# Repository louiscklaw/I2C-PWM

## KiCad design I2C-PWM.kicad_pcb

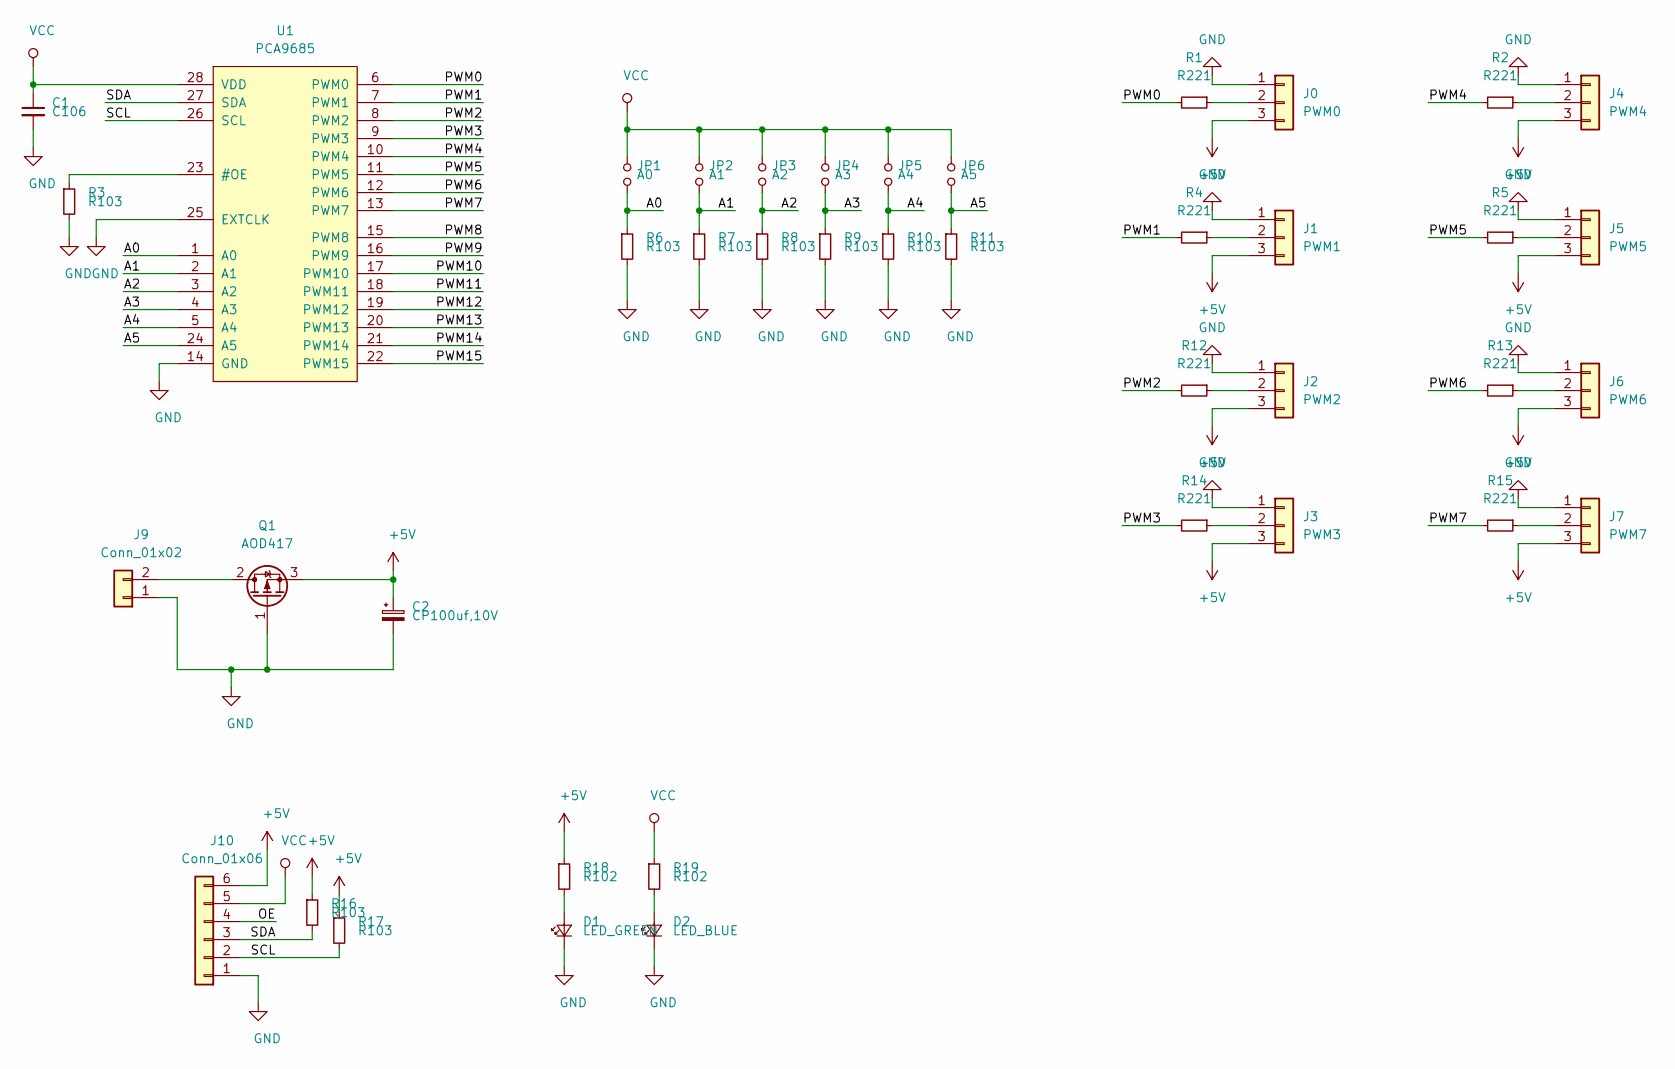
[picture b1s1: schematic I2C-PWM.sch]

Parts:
C1: C106; C_0805_2012Metric_Pad1.15x1.40mm_HandSolder
C2: CP100uf,10V; CP_Elec_6.3x5.2
D1: LED_GREEN; LED_0805_2012Metric_Pad1.15x1.40mm_HandSolder
D2: LED_BLUE; LED_0805_2012Metric_Pad1.15x1.40mm_HandSolder
J0: PWM0; PinHeader_1x03_P2.54mm_Vertical
J1: PWM1; PinHeader_1x03_P2.54mm_Vertical
J2: PWM2; PinHeader_1x03_P2.54mm_Vertical
J3: PWM3; PinHeader_1x03_P2.54mm_Vertical
J4: PWM4; PinHeader_1x03_P2.54mm_Vertical
J5: PWM5; PinHeader_1x03_P2.54mm_Vertical
J6: PWM6; PinHeader_1x03_P2.54mm_Vertical
J7: PWM7; PinHeader_1x03_P2.54mm_Vertical
J9: Conn_01x02; PinHeader_1x02_P2.54mm_Vertical
J10: Conn_01x06; PinHeader_1x06_P2.54mm_Vertical
JP1: A0; SolderJumper-2_P1.3mm_Open_TrianglePad1.0x1.5mm
JP2: A1; SolderJumper-2_P1.3mm_Open_TrianglePad1.0x1.5mm
JP3: A2; SolderJumper-2_P1.3mm_Open_TrianglePad1.0x1.5mm
JP4: A3; SolderJumper-2_P1.3mm_Open_TrianglePad1.0x1.5mm
JP5: A4; SolderJumper-2_P1.3mm_Open_TrianglePad1.0x1.5mm
JP6: A5; SolderJumper-2_P1.3mm_Open_TrianglePad1.0x1.5mm
Q1: AOD417; TO-252-2
R1, R2, R4, R5, R12, R13, R14, R15: R221; R_0805_2012Metric_Pad1.15x1.40mm_HandSolder
R3, R6, R7, R8, R9, R10, R11, R16, R17: R103; R_0805_2012Metric_Pad1.15x1.40mm_HandSolder
R18, R19: R102; R_0805_2012Metric_Pad1.15x1.40mm_HandSolder
U1: PCA9685; TSSOP-28_4.4x9.7mm_P0.65mm

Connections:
+5V: C2.1, J0.3, J1.3, J2.3, J3.3, J4.3, J5.3, J6.3, J7.3, J10.6, Q1.3 (S), R16.1, R17.1, R18.1
/A0: JP1.2, R6.1, U1.1 (A0)
/A1: JP2.2, R7.1, U1.2 (A1)
/A2: JP3.2, R8.1, U1.3 (A2)
/A3: JP4.2, R9.1, U1.4 (A3)
/A4: JP5.2, R10.1, U1.5 (A4)
/A5: JP6.2, R11.1, U1.24 (A5)
/OE: J10.4
/PWM0: R1.2, U1.6 (PWM0)
/PWM1: R4.2, U1.7 (PWM1)
/PWM2: R12.2, U1.8 (PWM2)
/PWM3: R14.2, U1.9 (PWM3)
/PWM4: R2.2, U1.10 (PWM4)
/PWM5: R5.2, U1.11 (PWM5)
/PWM6: R13.2, U1.12 (PWM6)
/PWM7: R15.2, U1.13 (PWM7)
/PWM8: U1.15 (PWM8)
/PWM9: U1.16 (PWM9)
/PWM10: U1.17 (PWM10)
/PWM11: U1.18 (PWM11)
/PWM12: U1.19 (PWM12)
/PWM13: U1.20 (PWM13)
/PWM14: U1.21 (PWM14)
/PWM15: U1.22 (PWM15)
/SCL: J10.2, R17.2, U1.26 (SCL)
/SDA: J10.3, R16.2, U1.27 (SDA)
GND: C1.2, C2.2, D1.1 (K), D2.1 (K), J0.1, J1.1, J2.1, J3.1, J4.1, J5.1, J6.1, J7.1, J9.1, J10.1, Q1.1 (G), R3.2, R6.2, R7.2, R8.2, R9.2, R10.2, R11.2, U1.14 (GND), U1.25 (EXTCLK)
unnamed: D1.2 (A), R18.2
unnamed: D2.2 (A), R19.2
unnamed: J0.2, R1.1
unnamed: J1.2, R4.1
unnamed: J2.2, R12.1
unnamed: J3.2, R14.1
unnamed: J4.2, R2.1
unnamed: J5.2, R5.1
unnamed: J6.2, R13.1
unnamed: J7.2, R15.1
unnamed: J9.2, Q1.2 (D)
unnamed: R3.1, U1.23 (#OE)
VCC: C1.1, J10.5, JP1.1, JP2.1, JP3.1, JP4.1, JP5.1, JP6.1, R19.1, U1.28 (VDD)

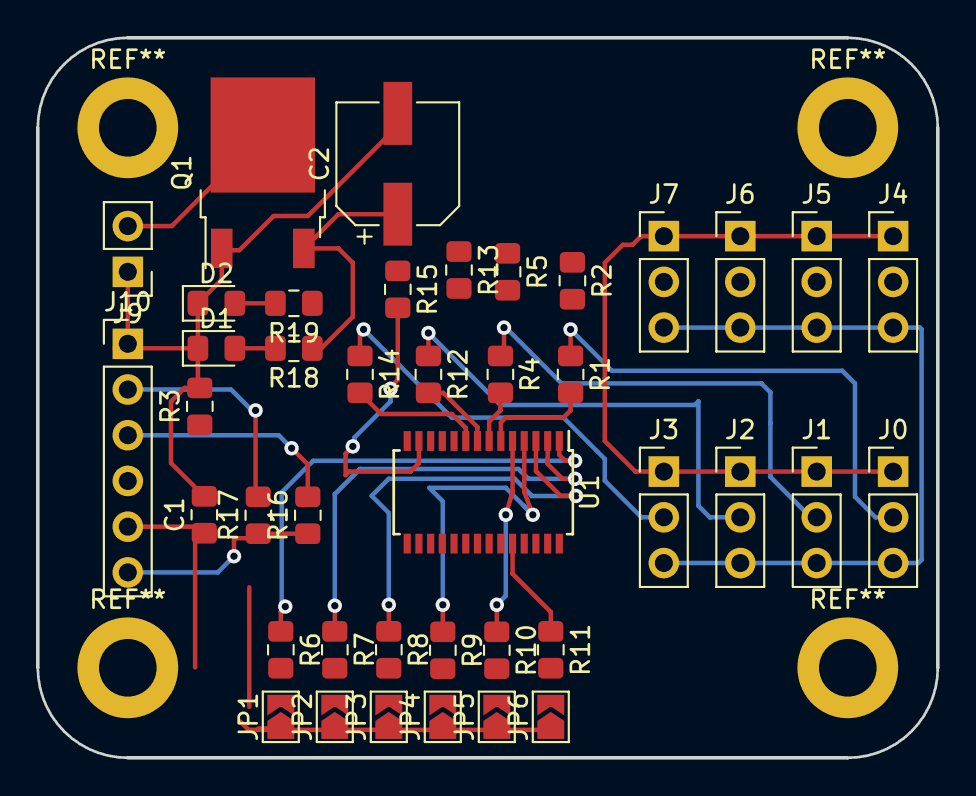
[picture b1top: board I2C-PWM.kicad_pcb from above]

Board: 2 copper layers, 50.0 x 40.0 mm, 41 parts (0 on the bottom side), 31 nets.

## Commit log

2018-10-17 update,
2020-05-05 ci: init travis build config,
2020-05-05 ci: init travis token,
